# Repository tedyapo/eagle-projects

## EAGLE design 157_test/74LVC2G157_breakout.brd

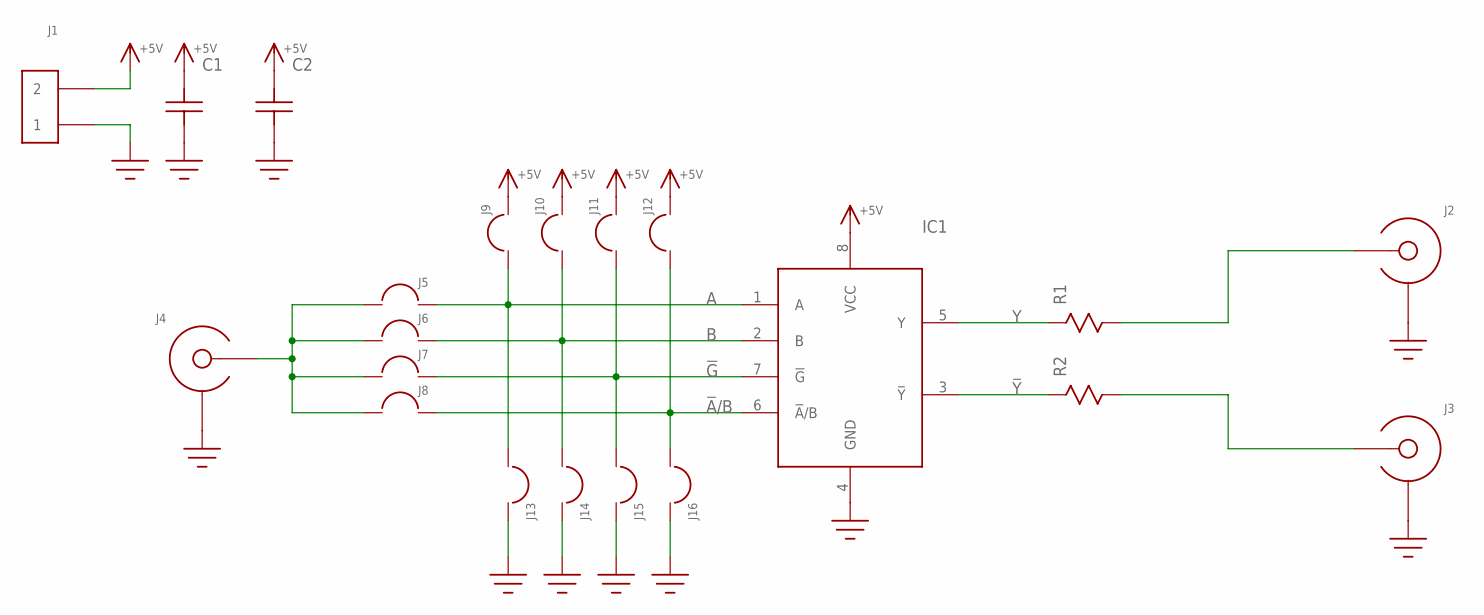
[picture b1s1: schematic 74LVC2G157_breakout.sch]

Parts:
C1: C0603
C2: C1206; 1206
IC1: 74LVC2G157; SSOP8
J1: HEADER_2PIN
J2, J3, J4: EDGE_LAUNCH_JACKNARROW; EDGE_LAUNCH_RF_CON_NARROW
J5, J6, J7, J8, J9, J10, J11, J12, J13, J14, J15, J16: SOLDER_BRIDGE
R1, R2: R0603

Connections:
!A!/B: IC1.6 (!A!/B), J8.2@1, J8.2@2, J8.2@3, J12.1, J16.1
!G!: IC1.7 (!G!), J7.2@1, J7.2@2, J7.2@3, J11.1, J15.1
!Y!: IC1.3 (!Y!), R2.P$1
+5V: C1.P$2, C2.P$2, IC1.8 (VCC), J1.2, J9.2@1, J9.2@2, J9.2@3, J10.2@1, J10.2@2, J10.2@3, J11.2@1, J11.2@2, J11.2@3, J12.2@1, J12.2@2, J12.2@3
A: IC1.1 (A), J5.2@1, J5.2@2, J5.2@3, J9.1, J13.1
B: IC1.2 (B), J6.2@1, J6.2@2, J6.2@3, J10.1, J14.1
GND: C1.P$1, C2.P$1, IC1.4 (GND), J1.1, J2.GND@1 (SHIELD), J2.GND@2 (SHIELD), J2.GND@3 (SHIELD), J2.GND@4 (SHIELD), J2.GND@5 (SHIELD), J2.GND@6 (SHIELD), J2.SHIELD@1 (SHIELD), J2.SHIELD@2 (SHIELD), J3.GND@1 (SHIELD), J3.GND@2 (SHIELD), J3.GND@3 (SHIELD), J3.GND@4 (SHIELD), J3.GND@5 (SHIELD), J3.GND@6 (SHIELD), J3.SHIELD@1 (SHIELD), J3.SHIELD@2 (SHIELD), J4.GND@1 (SHIELD), J4.GND@2 (SHIELD), J4.GND@3 (SHIELD), J4.GND@4 (SHIELD), J4.GND@5 (SHIELD), J4.GND@6 (SHIELD), J4.SHIELD@1 (SHIELD), J4.SHIELD@2 (SHIELD), J13.2@1, J13.2@2, J13.2@3, J14.2@1, J14.2@2, J14.2@3, J15.2@1, J15.2@2, J15.2@3, J16.2@1, J16.2@2, J16.2@3
unnamed: J3.CENTER, R2.P$2
unnamed: J2.CENTER, R1.P$2
unnamed: J4.CENTER, J5.1, J6.1, J7.1, J8.1
Y: IC1.5 (Y), R1.P$1

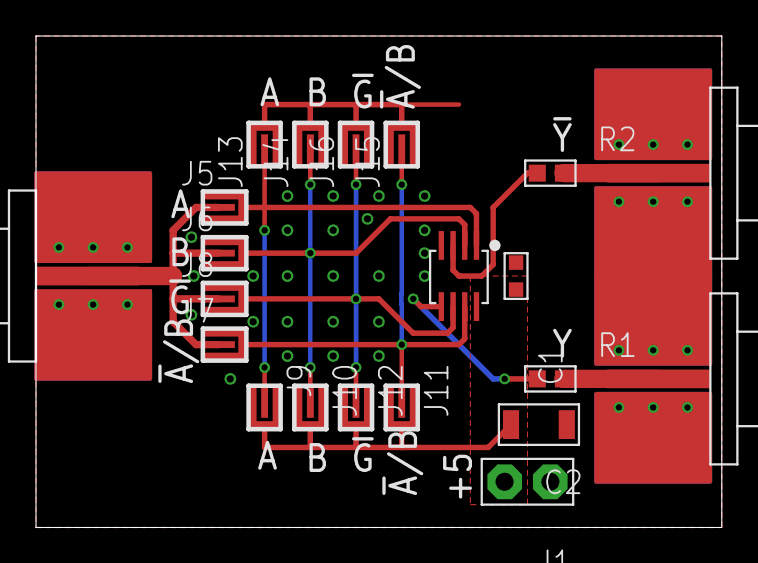
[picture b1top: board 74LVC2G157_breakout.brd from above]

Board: 2 copper layers, 38.1 x 27.3 mm, 21 parts (0 on the bottom side), 11 nets.

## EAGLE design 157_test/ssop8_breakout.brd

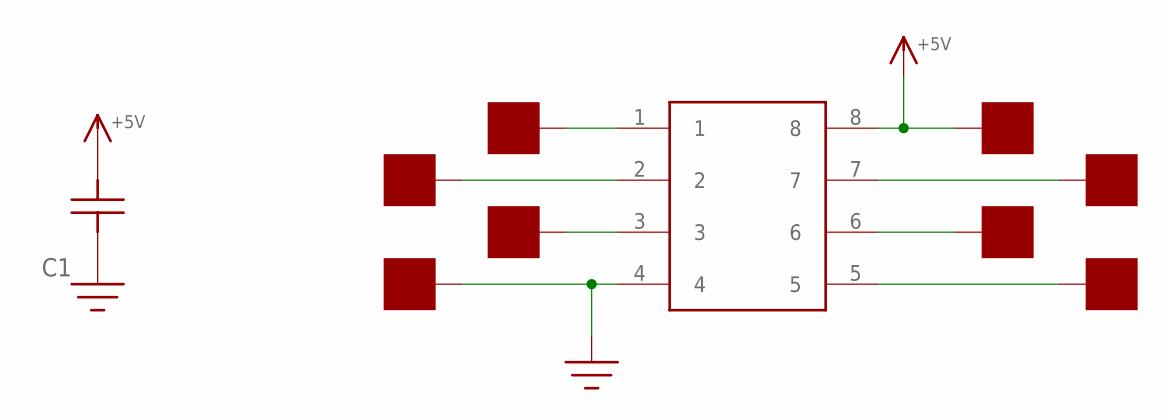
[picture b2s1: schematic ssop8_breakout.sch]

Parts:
C1: C0603
IC1: IC-8PINSSOP8; SSOP8
U$1, U$2, U$3, U$4, U$5, U$6, U$7, U$8: PAD50MIL; PAD_50MIL

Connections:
+5V: C1.P$1, IC1.8, U$1.P$1
GND: C1.P$2, IC1.4, U$8.P$1
unnamed: IC1.1, U$5.P$1
unnamed: IC1.2, U$6.P$1
unnamed: IC1.3, U$7.P$1
unnamed: IC1.7, U$2.P$1
unnamed: IC1.6, U$3.P$1
unnamed: IC1.5, U$4.P$1

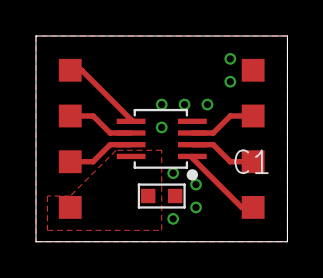
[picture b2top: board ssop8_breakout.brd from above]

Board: 2 copper layers, 14.0 x 11.4 mm, 10 parts (0 on the bottom side), 8 nets.

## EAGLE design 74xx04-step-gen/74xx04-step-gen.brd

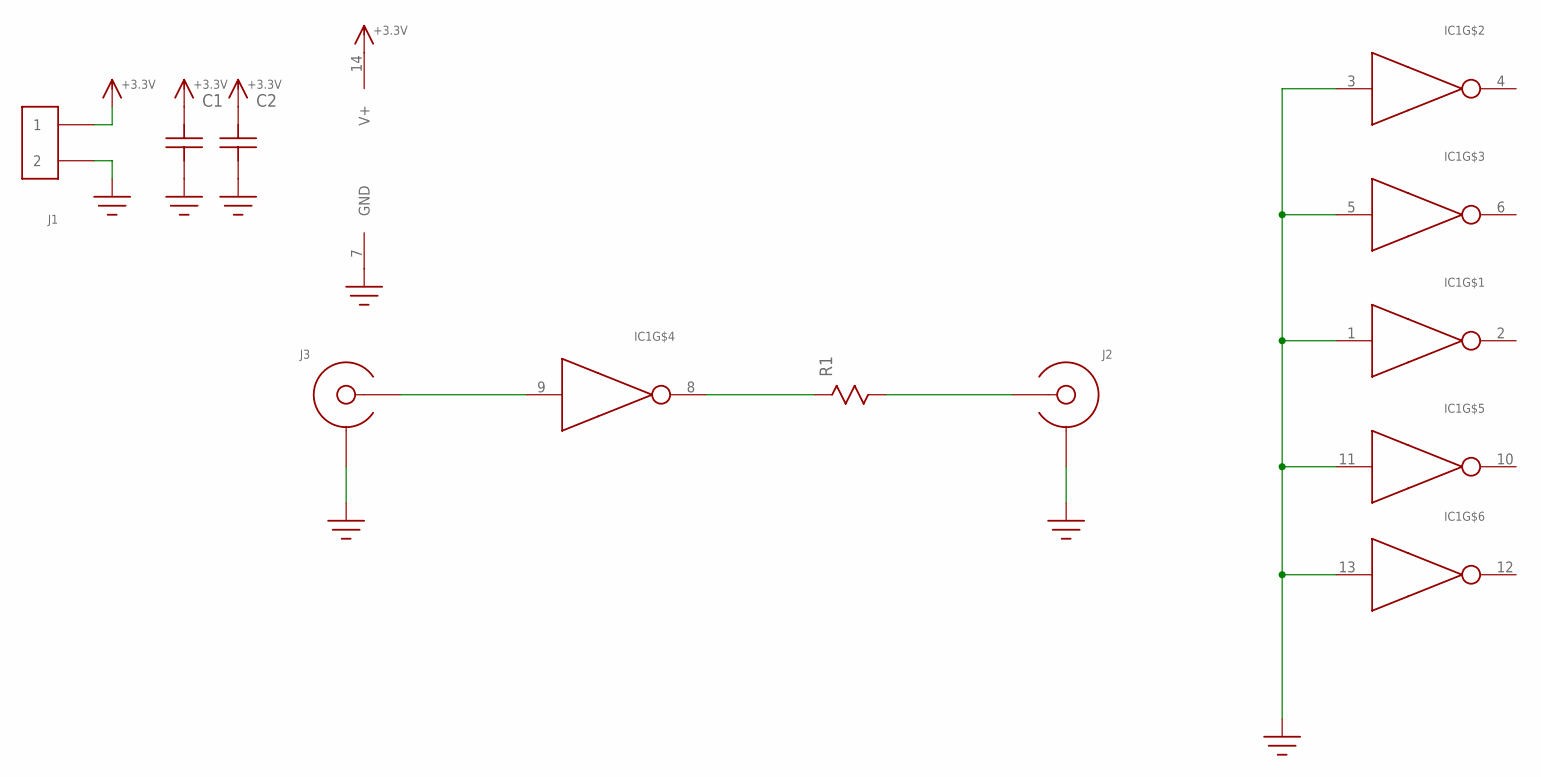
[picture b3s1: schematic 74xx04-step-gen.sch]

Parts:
C1: C1206; 1206
C2: C0603
IC1: 74XX04; SOIC-14
J1: HEADER_2PIN
J2, J3: SMA-EDGE-LAUNCH4020_TAPER; SMA_EDGE_LAUNCH_2L_4020_TAPER
R1: R0603

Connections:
+3.3V: C1.P$2, C2.P$2, IC1.14 (V+), J1.1
GND: C1.P$1, C2.P$1, IC1.1 (IN), IC1.3 (IN), IC1.5 (IN), IC1.7 (GND), IC1.11 (IN), IC1.13 (IN), J1.2, J2.BOTTOM_GND (SHIELD), J2.GND@1 (SHIELD), J2.GND@2 (SHIELD), J2.GND@3 (SHIELD), J2.GND@4 (SHIELD), J2.GND@5 (SHIELD), J2.GND@6 (SHIELD), J2.GND@7 (SHIELD), J2.GND@8 (SHIELD), J2.GND@14 (SHIELD), J2.GND@15 (SHIELD), J2.GND@16 (SHIELD), J2.GND@17 (SHIELD), J2.GND_PAD1 (SHIELD), J2.GND_PAD2 (SHIELD), J2.P$1 (SHIELD), J2.P$2 (SHIELD), J3.BOTTOM_GND (SHIELD), J3.GND@1 (SHIELD), J3.GND@2 (SHIELD), J3.GND@3 (SHIELD), J3.GND@4 (SHIELD), J3.GND@5 (SHIELD), J3.GND@6 (SHIELD), J3.GND@7 (SHIELD), J3.GND@8 (SHIELD), J3.GND@14 (SHIELD), J3.GND@15 (SHIELD), J3.GND@16 (SHIELD), J3.GND@17 (SHIELD), J3.GND_PAD1 (SHIELD), J3.GND_PAD2 (SHIELD), J3.P$1 (SHIELD), J3.P$2 (SHIELD)
unnamed: IC1.9 (IN), J3.CENTER@1 (CENTER)
unnamed: IC1.8 (OUT), R1.P$1
unnamed: J2.CENTER@1 (CENTER), R1.P$2

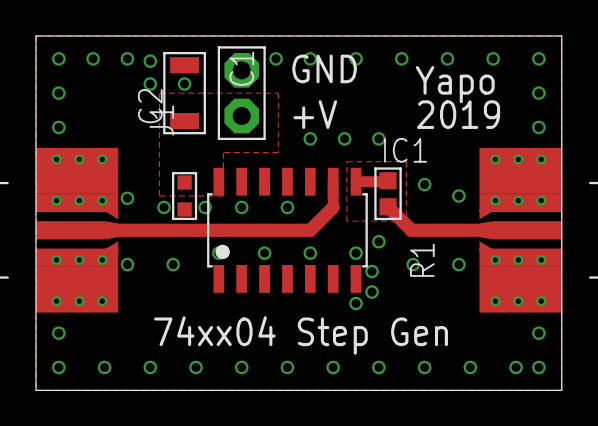
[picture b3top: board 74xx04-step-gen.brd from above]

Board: 2 copper layers, 29.2 x 19.7 mm, 7 parts (0 on the bottom side), 5 nets.

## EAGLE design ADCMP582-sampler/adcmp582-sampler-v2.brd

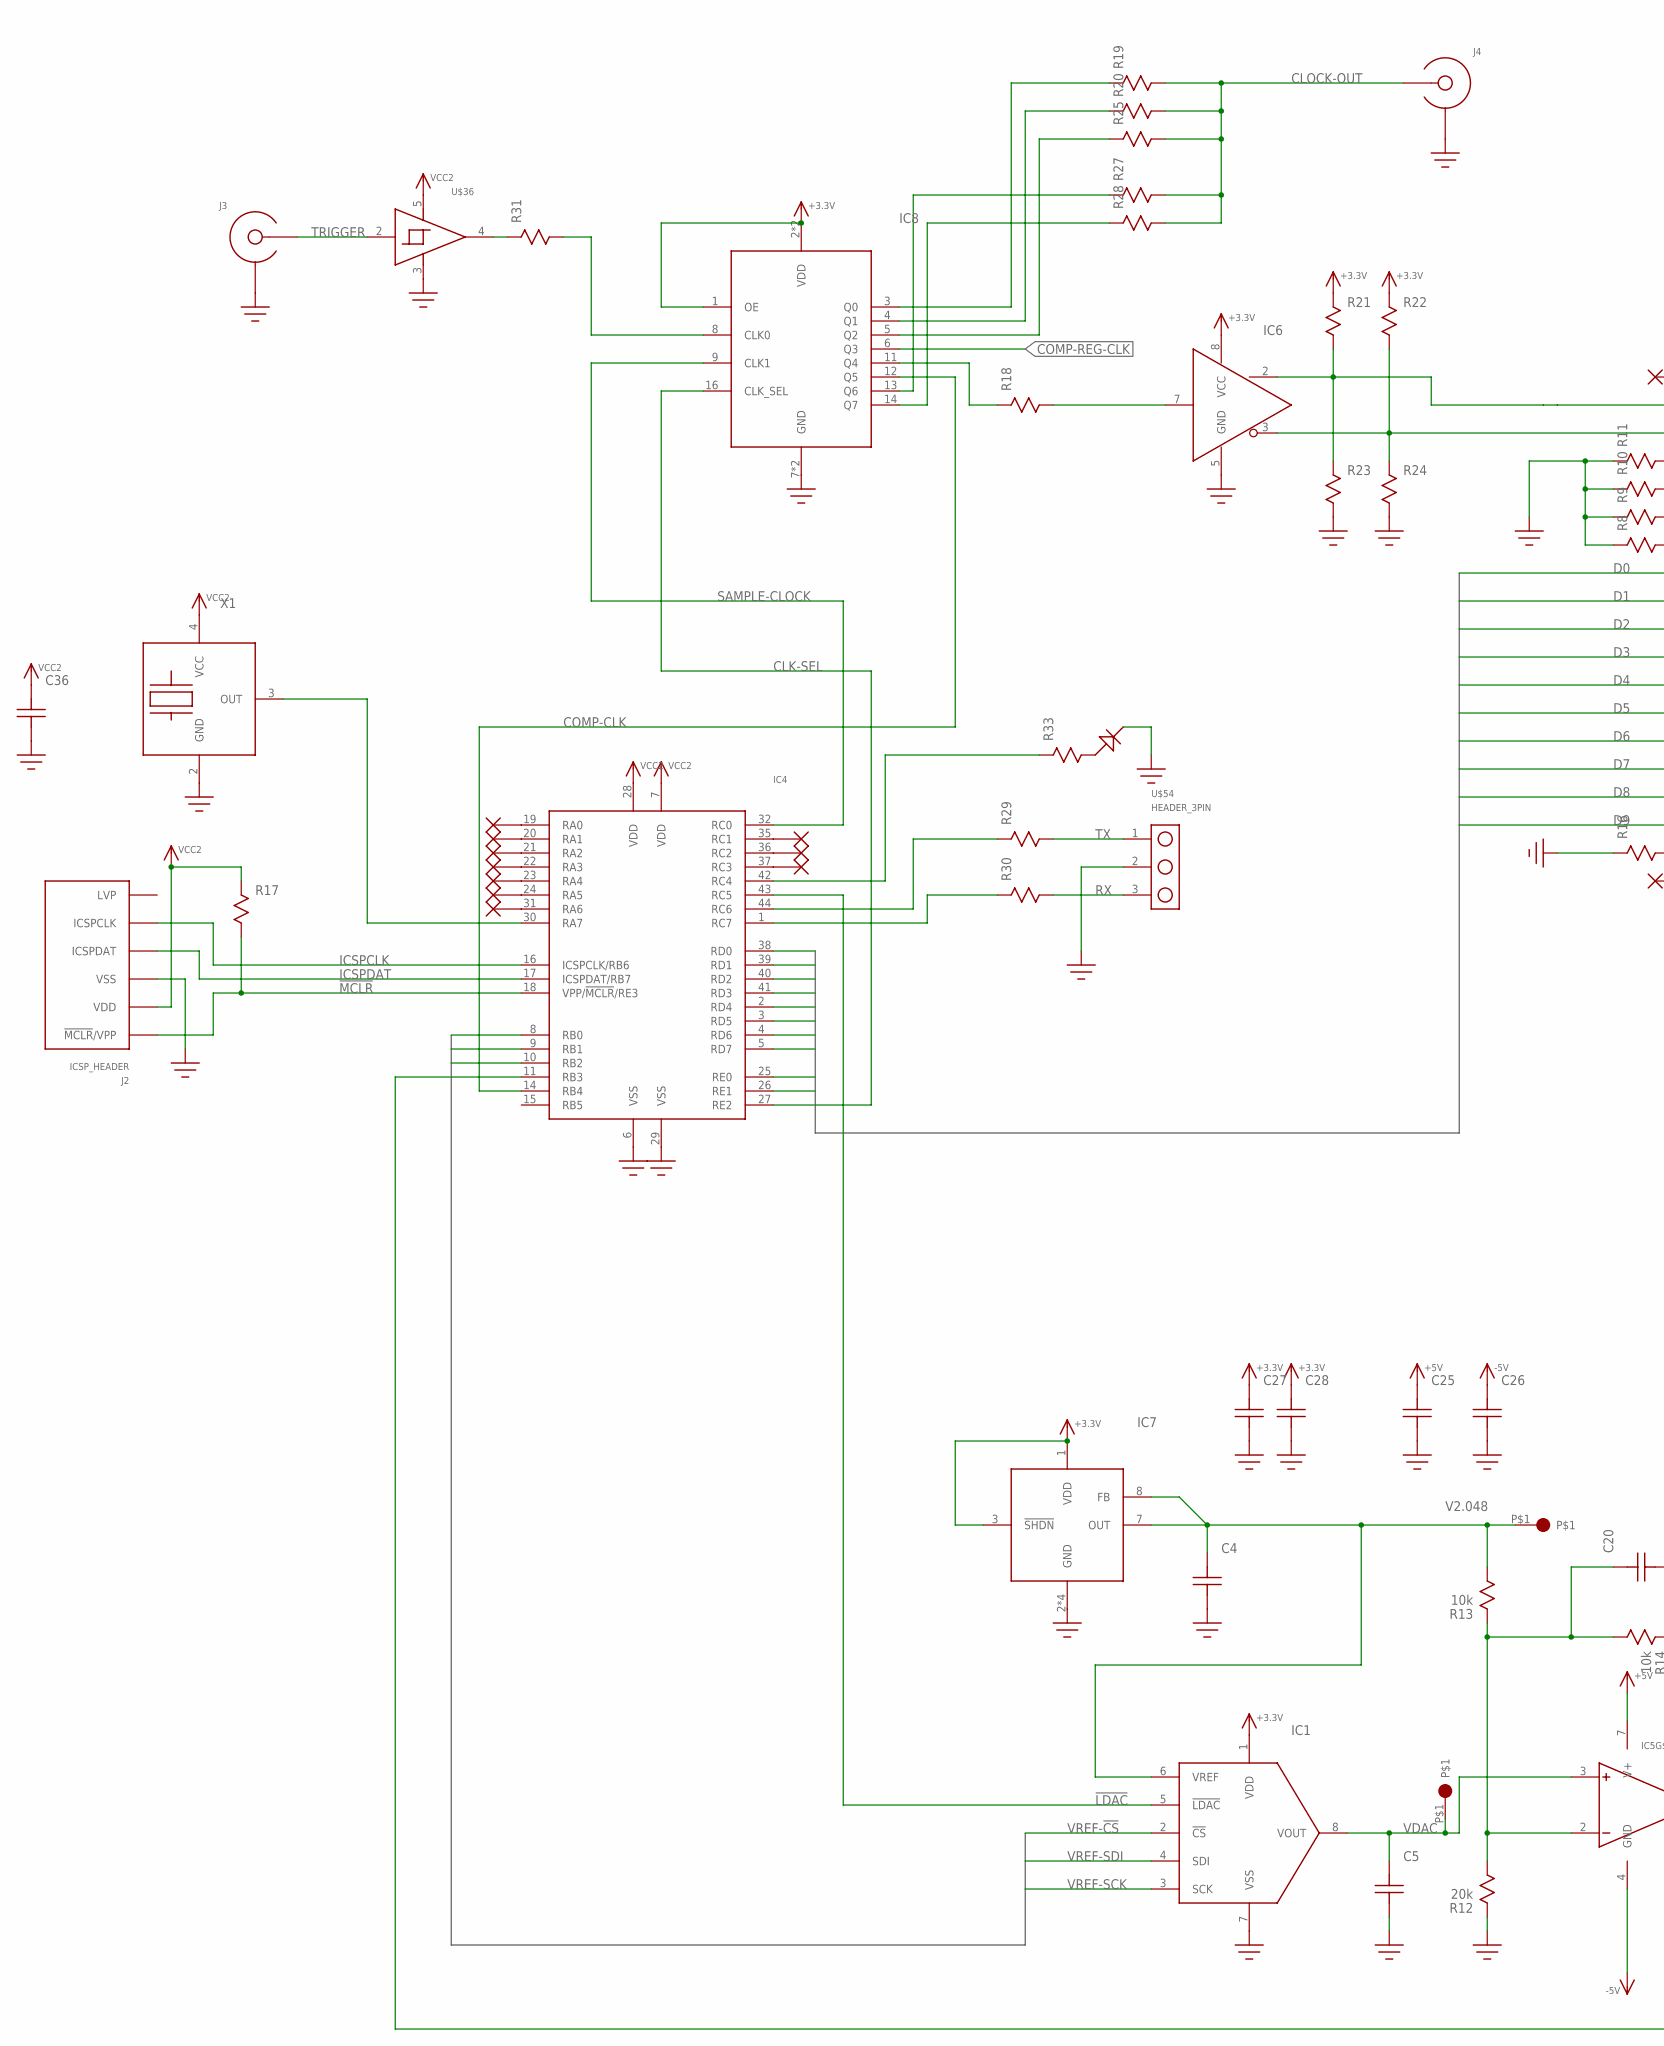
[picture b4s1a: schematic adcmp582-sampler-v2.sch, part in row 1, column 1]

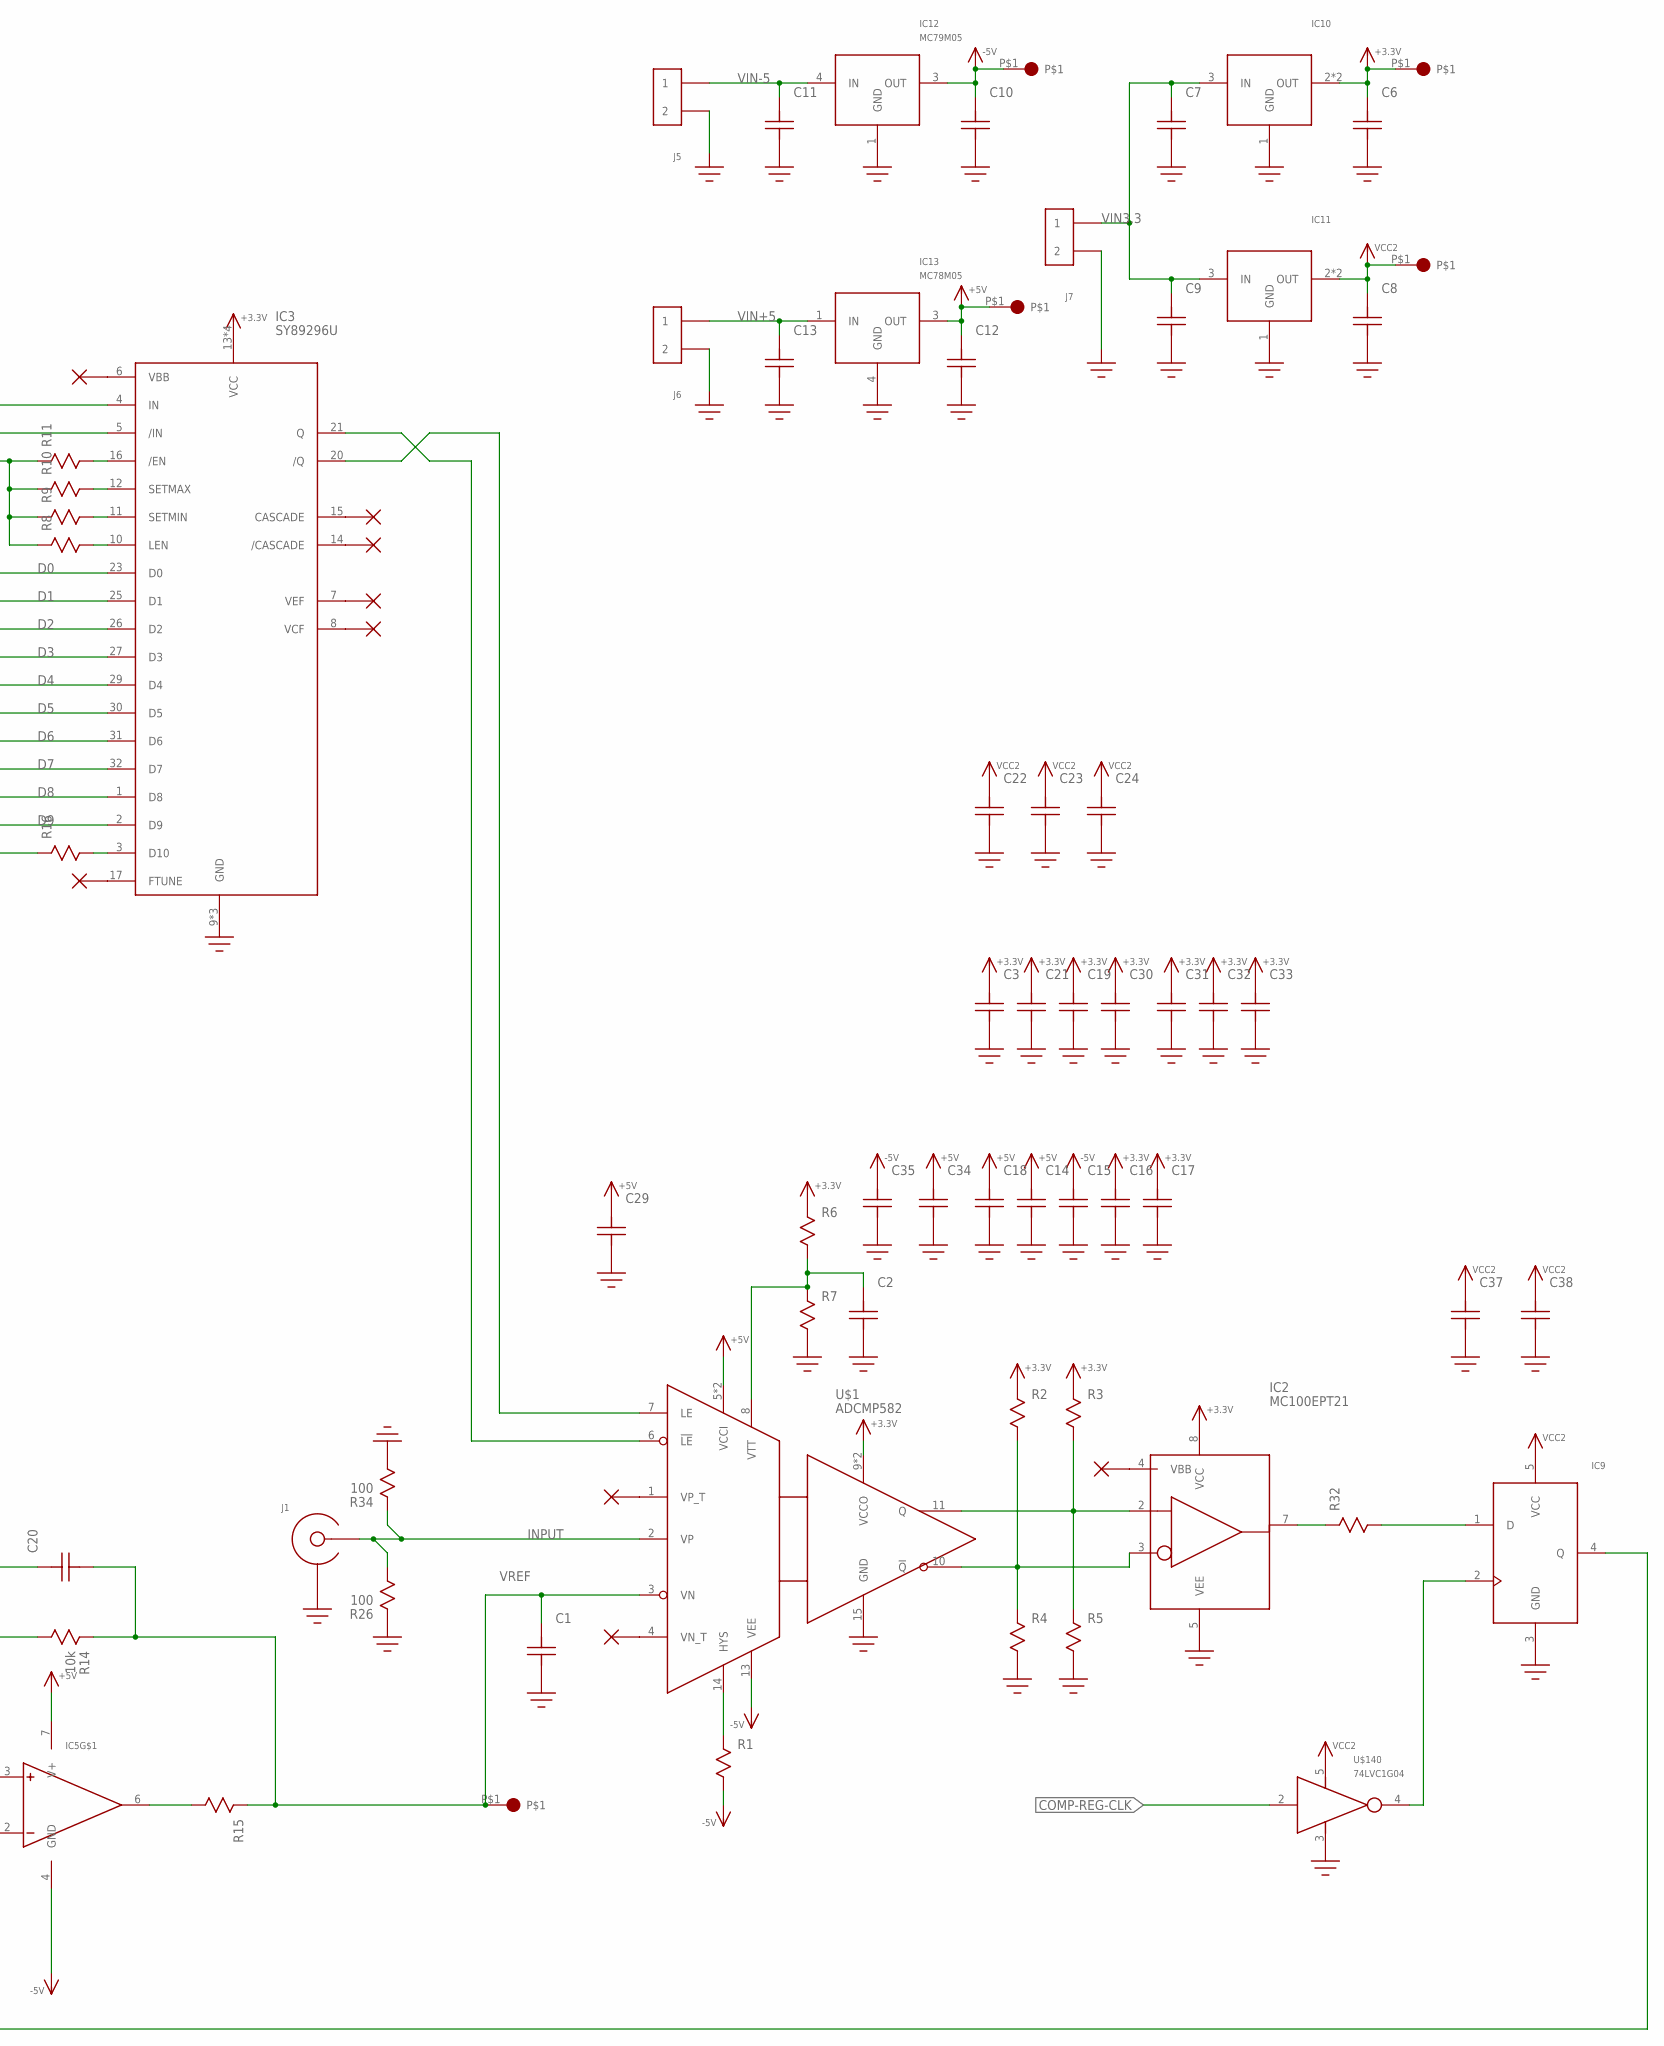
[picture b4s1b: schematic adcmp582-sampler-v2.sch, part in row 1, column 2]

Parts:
C1, C3, C4, C5, C19, C20, C21, C22, C23, C24, C25, C26, C27, C28, C30, C31, C32, C33, C34, C35, C36, C37, C38: C0603
C2, C14, C15, C16, C17, C18: C0402_NO_THERMALS
C6, C7, C8, C9, C10, C11, C12, C13, C29: C1206; 1206
IC1: MCP49X1; SOIC8
IC2: MC100EPT21; SOIC8
IC3: SY89296U; TQFP32_7X7
IC4: PIC16F15376; TQFP44
IC5: ADA4000; SOIC8
IC6: MC100LVELT20; SOIC8
IC7: MCP1501SOIC8; SOIC8
IC8: SI53360TSSOP16; TSSOP16
IC9: 74LVC1G79; SOT23-5
IC10, IC11: AZ1117E; SOT-223
IC12: MC79M05; DPAK
IC13: MC78M05; DPAK
J1, J3, J4: SMA-EDGE-LAUNCH4L-4020-TAPER-FIXED; SMA_EDGE_LAUNCH_4L_4020_TAPER_FIXED
J2: ICSP_HEADER; HEADER_6PIN
J5, J6, J7: HEADER_2PINSCREW-TERM; FCI_20020316_SCREW_TERM_2P
P1, P2, P3, P4, P5, P6, P7: ICSP_PAD
R1, R2, R3, R4, R5, R6, R7, R15, R16, R17, R18, R21, R22, R23, R24, R29, R30, R31, R32, R33: R0603
R8, R9, R10, R11, R19, R20, R25, R27, R28: R0402; 0402
R12: 20k; R0603
R13, R14: 10k; R0603
R26, R34: 100; 0402
U$1: ADCMP582; TQFN16-EP
U$36: 74LVC1G17; SOT23-5
U$54: HEADER_3PIN
U$88: LED_0603
U$140: 74LVC1G04; SOT23-5
X1: XTAL_OSC; XTAL_3.2X5

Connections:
!LDAC!: IC1.5 (!LDAC!), IC4.43 (RC5)
!MCLR!: IC4.18 (VPP/!MCLR!/RE3), J2.1 (!MCLR!/VPP), R17.P$2
+3.3V: C3.P$2, C6.P$2, C16.2, C17.2, C19.P$2, C21.P$2, C27.P$2, C28.P$2, C30.P$2, C31.P$2, C32.P$2, C33.P$2, IC1.1 (VDD), IC2.8 (VCC), IC3.13 (VCC), IC3.18 (VCC), IC3.19 (VCC), IC3.22 (VCC), IC6.8 (VCC), IC7.1 (VDD), IC7.3 (!SHDN!), IC8.1 (OE), IC8.2 (VDD), IC8.15 (VDD), IC10.2 (OUT), IC10.4 (OUT), P5.P$1, R2.P$1, R3.P$1, R6.P$1, R21.P$1, R22.P$1, U$1.9 (VCCO), U$1.12 (VCCO)
+5V: C12.P$2, C14.2, C18.2, C25.P$2, C29.P$2, C34.P$2, IC5.7 (V+), IC13.3 (OUT), P4.P$1, U$1.5 (VCCI), U$1.16 (VCCI)
-5V: C10.P$2, C15.2, C26.P$2, C35.P$2, IC5.4 (GND), IC12.3 (OUT), P3.P$1, R1.P$2, U$1.13 (VEE)
CLK-SEL: IC4.27 (RE2), IC8.16 (CLK_SEL)
CLOCK-OUT: J4.CENTER@1 (CENTER), J4.P$3 (CENTER), R19.2, R20.2, R25.2, R27.2, R28.2
COMP-CLK: IC4.14 (RB4), IC8.12 (Q5)
COMP-OUT: IC4.11 (RB3), IC9.4 (Q)
COMP-REG-CLK: IC8.6 (Q3), U$140.2 (IN)
D0: IC3.23 (D0), IC4.38 (RD0)
D1: IC3.25 (D1), IC4.39 (RD1)
D2: IC3.26 (D2), IC4.40 (RD2)
D3: IC3.27 (D3), IC4.41 (RD3)
D4: IC3.29 (D4), IC4.2 (RD4)
D5: IC3.30 (D5), IC4.3 (RD5)
D6: IC3.31 (D6), IC4.4 (RD6)
D7: IC3.32 (D7), IC4.5 (RD7)
D8: IC3.1 (D8), IC4.25 (RE0)
D9: IC3.2 (D9), IC4.26 (RE1)
GND: C1.P$1, C2.1, C3.P$1, C4.P$1, C5.P$1, C6.P$1, C7.P$1, C8.P$1, C9.P$1, C10.P$1, C11.P$1, C12.P$1, C13.P$1, C14.1, C15.1, C16.1, C17.1, C18.1, C19.P$1, C21.P$1, C22.P$1, C23.P$1, C24.P$1, C25.P$1, C26.P$1, C27.P$1, C28.P$1, C29.P$1, C30.P$1, C31.P$1, C32.P$1, C33.P$1, C34.P$1, C35.P$1, C36.P$1, C37.P$1, C38.P$1, IC1.7 (VSS), IC2.5 (VEE), IC3.9 (GND), IC3.24 (GND), IC3.28 (GND), IC4.6 (VSS), IC4.29 (VSS), IC6.5 (GND), IC7.2 (GND), IC7.4 (GND), IC7.5 (GND), IC7.6 (GND), IC8.7 (GND), IC8.10 (GND), IC9.3 (GND), IC10.1 (GND), IC11.1 (GND), IC12.1 (GND), IC13.4 (GND), J1.BOTTOM_GND (SHIELD), J1.GND@1 (SHIELD), J1.GND@2 (SHIELD), J1.GND@3 (SHIELD), J1.GND@4 (SHIELD), J1.GND@5 (SHIELD), J1.GND@6 (SHIELD), J1.GND@7 (SHIELD), J1.GND@8 (SHIELD), J1.GND@14 (SHIELD), J1.GND@15 (SHIELD), J1.GND@16 (SHIELD), J1.GND@17 (SHIELD), J1.GND_PAD1 (SHIELD), J1.GND_PAD2 (SHIELD), J1.P$1 (SHIELD), J1.P$2 (SHIELD), J2.3 (VSS), J3.BOTTOM_GND (SHIELD), J3.GND@1 (SHIELD), J3.GND@2 (SHIELD), J3.GND@3 (SHIELD), J3.GND@4 (SHIELD), J3.GND@5 (SHIELD), J3.GND@6 (SHIELD), J3.GND@7 (SHIELD), J3.GND@8 (SHIELD), J3.GND@14 (SHIELD), J3.GND@15 (SHIELD), J3.GND@16 (SHIELD), J3.GND@17 (SHIELD), J3.GND_PAD1 (SHIELD), J3.GND_PAD2 (SHIELD), J3.P$1 (SHIELD), J3.P$2 (SHIELD), J4.BOTTOM_GND (SHIELD), J4.GND@1 (SHIELD), J4.GND@2 (SHIELD), J4.GND@3 (SHIELD), J4.GND@4 (SHIELD), J4.GND@5 (SHIELD), J4.GND@6 (SHIELD), J4.GND@7 (SHIELD), J4.GND@8 (SHIELD), J4.GND@14 (SHIELD), J4.GND@15 (SHIELD), J4.GND@16 (SHIELD), J4.GND@17 (SHIELD), J4.GND_PAD1 (SHIELD), J4.GND_PAD2 (SHIELD), J4.P$1 (SHIELD), J4.P$2 (SHIELD), J5.P$2 (2), J6.P$2 (2), J7.P$2 (2), R4.P$2, R5.P$2, R7.P$2, R8.1, R9.1, R10.1, R11.1, R12.P$1, R16.P$1, R23.P$2, R24.P$2, R26.1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
ICSPCLK: IC4.16 (ICSPCLK/RB6), J2.5 (ICSPCLK)
ICSPDAT: IC4.17 (ICSPDAT/RB7), J2.4 (ICSPDAT)
INPUT: J1.CENTER@1 (CENTER), J1.P$3 (CENTER), R26.2, R34.1, U$1.2 (VP)
LE_N: IC3.21 (Q), U$1.6 (!LE!)
LE_P1: IC3.20 (/Q), U$1.7 (LE)
unnamed: R31.P$1, U$36.4 (OUT)
unnamed: R1.P$1, U$1.14 (HYS)
unnamed: IC2.2 (D), R3.P$2, R5.P$1, U$1.11 (Q)
unnamed: IC2.3 (!D!), R2.P$2, R4.P$1, U$1.10 (!Q!)
unnamed: C2.2, R6.P$2, R7.P$1, U$1.8 (VTT)
unnamed: IC3.16 (/EN), R11.2
unnamed: IC3.12 (SETMAX), R10.2
unnamed: IC3.11 (SETMIN), R9.2
unnamed: IC3.10 (LEN), R8.2
unnamed: IC3.4 (IN), IC6.2 (Q), R21.P$2, R23.P$1
unnamed: IC2.7 (Q), R32.P$1
unnamed: IC8.11 (Q4), R18.P$1
unnamed: IC9.2 (CLK), U$140.4 (OUT)
unnamed: C20.P$2, IC5.2 (-), R12.P$2, R13.P$1, R14.P$2
unnamed: IC3.5 (/IN), IC6.3 (!Q!), R22.P$2, R24.P$1
unnamed: IC8.8 (CLK0), R31.P$2
unnamed: IC4.30 (RA7), X1.3 (OUT)
unnamed: IC4.42 (RC4), R33.P$1
unnamed: R33.P$2, U$88.A
unnamed: IC9.1 (D), R32.P$2
unnamed: IC5.6 (OUT), R15.P$2
unnamed: IC3.3 (D10), R16.P$2
unnamed: IC6.7 (D), R18.P$2
unnamed: IC8.14 (Q7), R28.1
unnamed: IC8.13 (Q6), R27.1
unnamed: IC8.5 (Q2), R25.1
unnamed: IC8.4 (Q1), R20.1
unnamed: IC8.3 (Q0), R19.1
unnamed: IC4.44 (RC6), R29.P$1
unnamed: IC4.1 (RC7), R30.P$1
RX: R30.P$2, U$54.3
SAMPLE-CLOCK: IC4.32 (RC0), IC8.9 (CLK1)
TRIGGER: J3.CENTER@1 (CENTER), J3.P$3 (CENTER), U$36.2 (IN)
TX: R29.P$2, U$54.1
V2.048: C4.P$2, IC1.6 (VREF), IC7.7 (OUT), IC7.8 (FB), P7.P$1, R13.P$2
VCC2: C8.P$2, C22.P$2, C23.P$2, C24.P$2, C36.P$2, C37.P$2, C38.P$2, IC4.7 (VDD), IC4.28 (VDD), IC9.5 (VCC), IC11.2 (OUT), IC11.4 (OUT), J2.2 (VDD), P6.P$1, R17.P$1, U$36.5 (VCC), U$140.5 (VCC), X1.4 (VCC)
VDAC: C5.P$2, IC1.8 (VOUT), IC5.3 (+), P2.P$1
VIN3.3: C7.P$2, C9.P$2, IC10.3 (IN), IC11.3 (IN), J7.P$1 (1)
VIN+5: C13.P$2, IC13.1 (IN), J6.P$1 (1)
VIN-5: C11.P$2, IC12.4 (IN), J5.P$1 (1)
VREF: C1.P$2, C20.P$1, P1.P$1, R14.P$1, R15.P$1, U$1.3 (VN)
VREF-!CS!: IC1.2 (!CS!), IC4.8 (RB0)
VREF-SCK: IC1.3 (SCK), IC4.9 (RB1)
VREF-SDI: IC1.4 (SDI), IC4.10 (RB2)

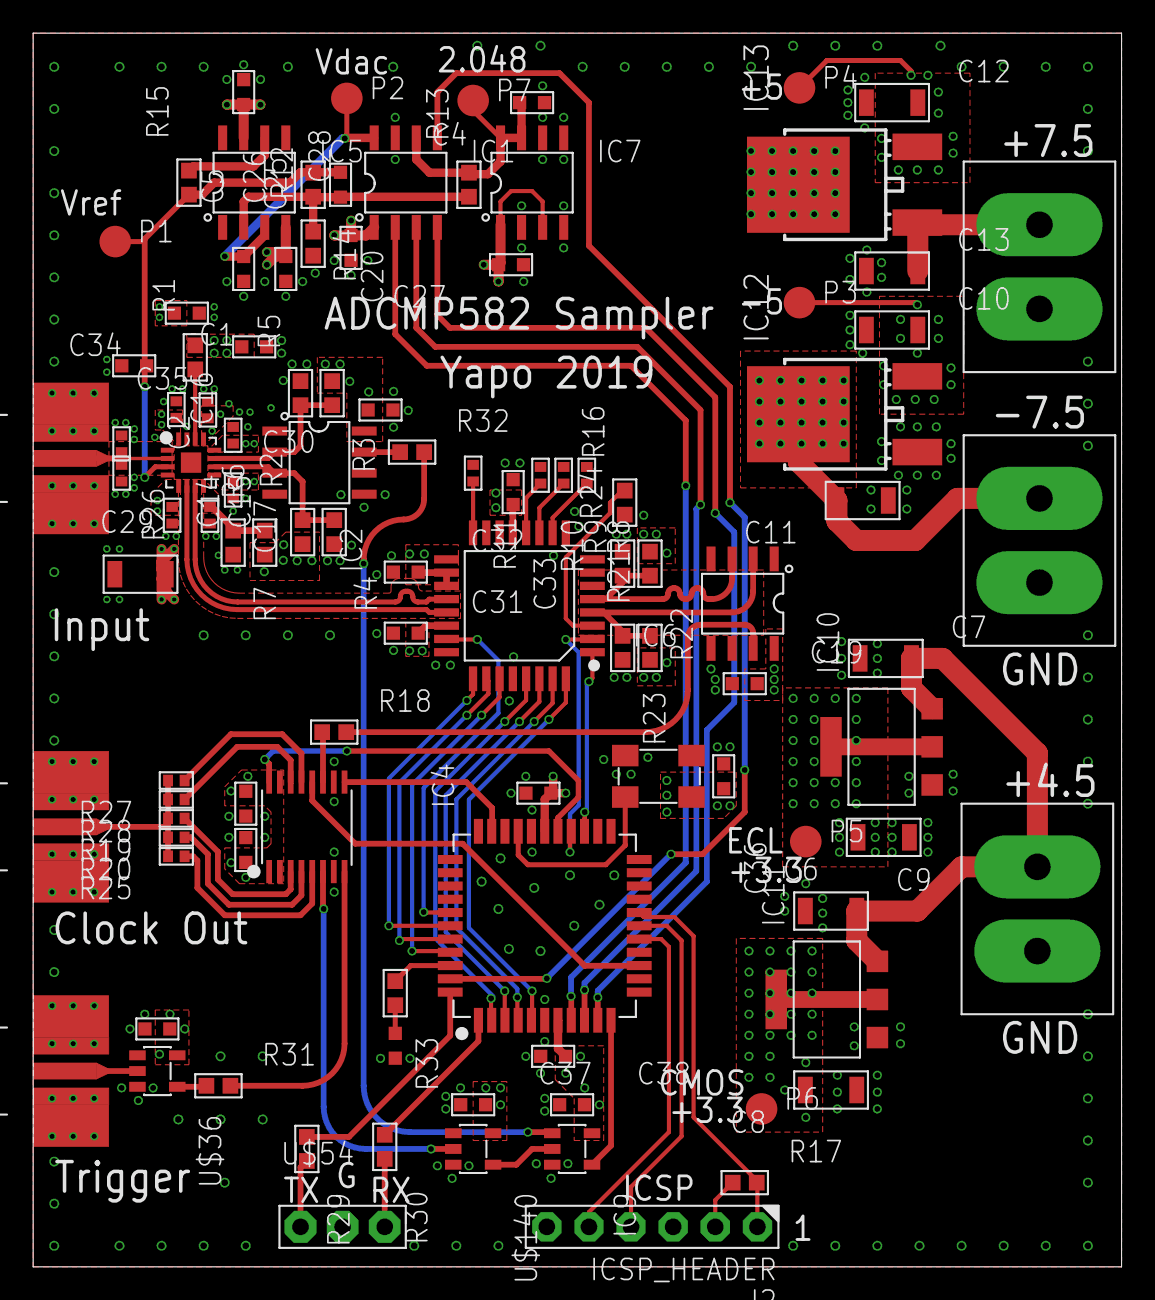
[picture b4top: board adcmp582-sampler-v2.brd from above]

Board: 4 copper layers, 65.7 x 74.4 mm, 105 parts (0 on the bottom side), 70 nets.

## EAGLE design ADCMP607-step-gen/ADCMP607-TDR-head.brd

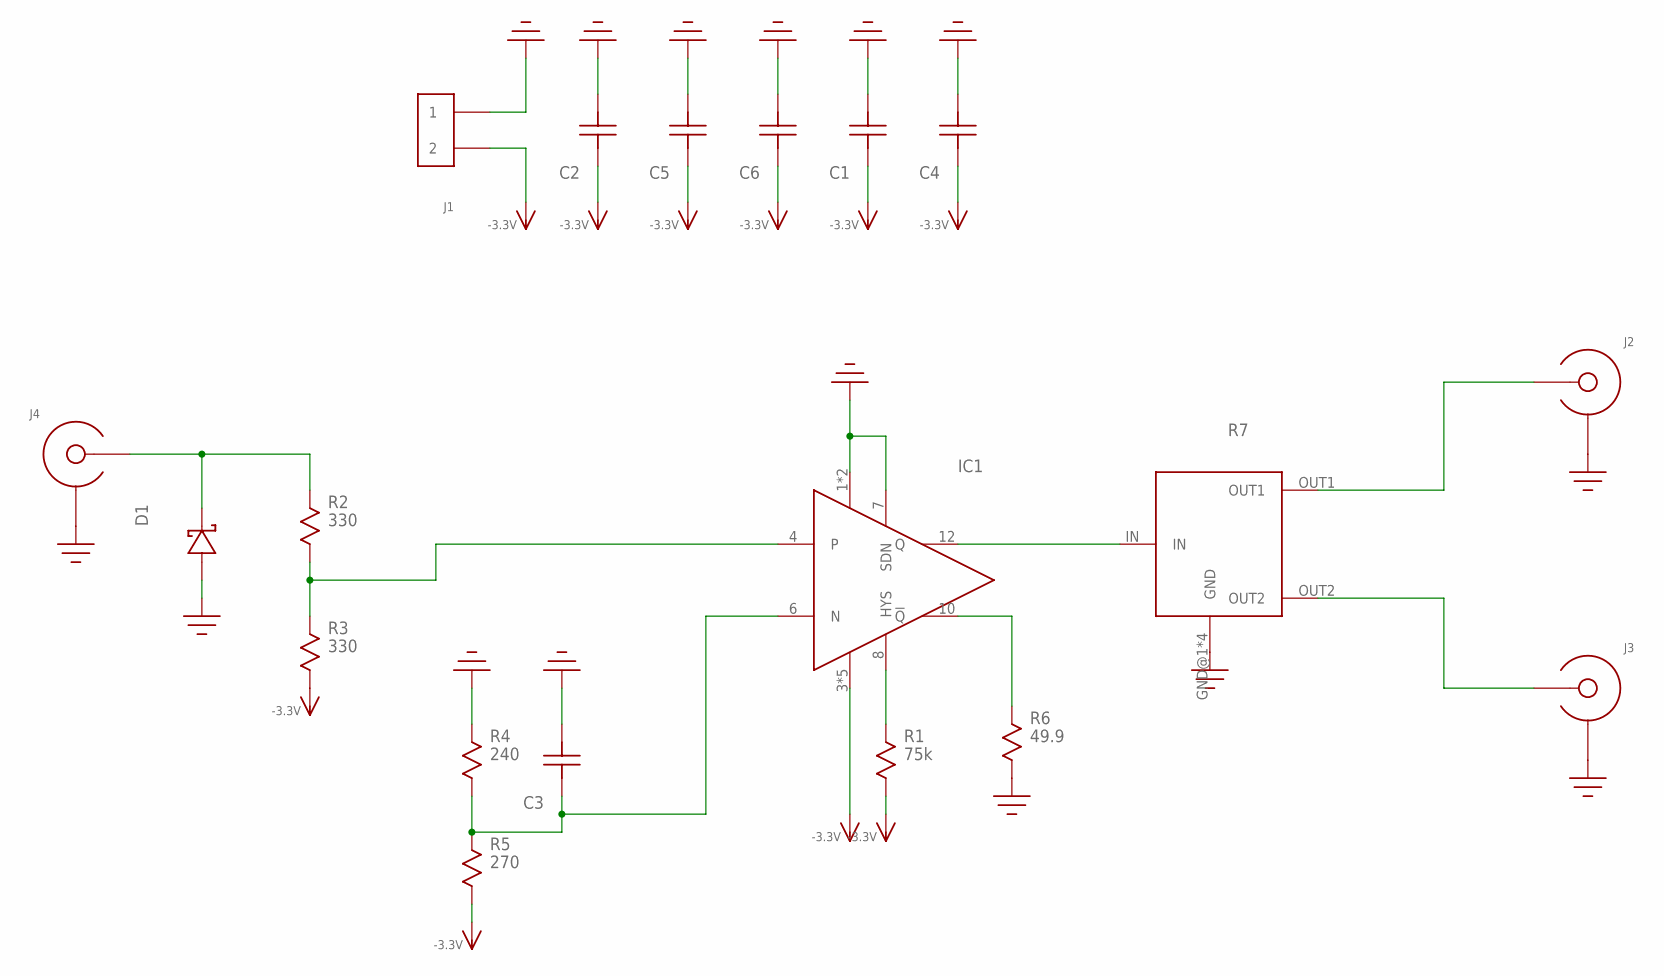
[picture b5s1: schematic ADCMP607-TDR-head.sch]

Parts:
C1, C3, C4, C5, C6: C0603
C2: C1206; 1206
D1: SCHOTTKYSOT-23; SOT-23
IC1: ADCMP607; QFN12-3X3
J1: HEADER_2PIN
J2, J3, J4: SMA-EDGE-LAUNCH4020_TAPER; SMA_EDGE_LAUNCH_2L_4020_TAPER
R1: 75k; R0603
R2, R3: 330; R0603
R4: 240; R0603
R5: 270; R0603
R6: 49.9; 0402
R7: PS2012G-SPLITTER

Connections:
-3.3V: C1.P$2, C2.P$2, C4.P$2, C5.P$2, C6.P$2, IC1.3 (VEE), IC1.5 (VEE), IC1.9 (VEE), IC1.11 (VEE), IC1.EP (VEE), J1.2, R1.P$2, R3.P$2, R5.P$2
GND: C1.P$1, C2.P$1, C3.P$1, C4.P$1, C5.P$1, C6.P$1, D1.1 (ANODE), IC1.1 (VCC), IC1.2 (VCC), IC1.7 (SDN), J1.1, J2.BOTTOM_GND (SHIELD), J2.GND@1 (SHIELD), J2.GND@2 (SHIELD), J2.GND@3 (SHIELD), J2.GND@4 (SHIELD), J2.GND@5 (SHIELD), J2.GND@6 (SHIELD), J2.GND@7 (SHIELD), J2.GND@8 (SHIELD), J2.GND@14 (SHIELD), J2.GND@15 (SHIELD), J2.GND@16 (SHIELD), J2.GND@17 (SHIELD), J2.GND_PAD1 (SHIELD), J2.GND_PAD2 (SHIELD), J2.P$1 (SHIELD), J2.P$2 (SHIELD), J3.BOTTOM_GND (SHIELD), J3.GND@1 (SHIELD), J3.GND@2 (SHIELD), J3.GND@3 (SHIELD), J3.GND@4 (SHIELD), J3.GND@5 (SHIELD), J3.GND@6 (SHIELD), J3.GND@7 (SHIELD), J3.GND@8 (SHIELD), J3.GND@14 (SHIELD), J3.GND@15 (SHIELD), J3.GND@16 (SHIELD), J3.GND@17 (SHIELD), J3.GND_PAD1 (SHIELD), J3.GND_PAD2 (SHIELD), J3.P$1 (SHIELD), J3.P$2 (SHIELD), J4.BOTTOM_GND (SHIELD), J4.GND@1 (SHIELD), J4.GND@2 (SHIELD), J4.GND@3 (SHIELD), J4.GND@4 (SHIELD), J4.GND@5 (SHIELD), J4.GND@6 (SHIELD), J4.GND@7 (SHIELD), J4.GND@8 (SHIELD), J4.GND@14 (SHIELD), J4.GND@15 (SHIELD), J4.GND@16 (SHIELD), J4.GND@17 (SHIELD), J4.GND_PAD1 (SHIELD), J4.GND_PAD2 (SHIELD), J4.P$1 (SHIELD), J4.P$2 (SHIELD), R4.P$1, R6.2, R7.GND@1 (GND), R7.GND@2 (GND), R7.GND@3 (GND), R7.GND@4 (GND)
unnamed: C3.P$2, IC1.6 (N), R4.P$2, R5.P$1
unnamed: IC1.8 (HYS), R1.P$1
unnamed: IC1.12 (Q), R7.IN
unnamed: IC1.10 (!Q!), R6.1
unnamed: D1.3 (CATHODE), J4.CENTER@1 (CENTER), R2.P$1
unnamed: IC1.4, R2.P$2, R3.P$1
unnamed: J2.CENTER@1 (CENTER), R7.OUT1
unnamed: J3.CENTER@1 (CENTER), R7.OUT2

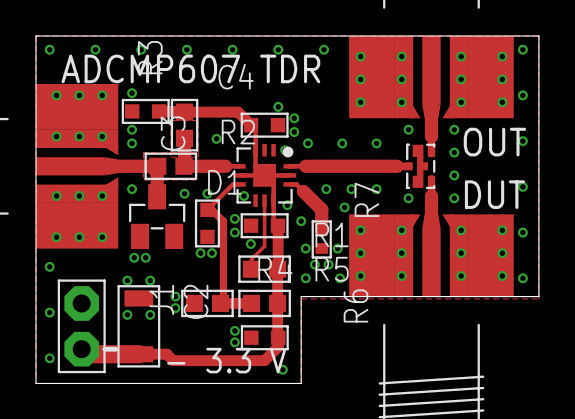
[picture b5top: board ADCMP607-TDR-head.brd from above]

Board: 2 copper layers, 27.9 x 19.3 mm, 19 parts (0 on the bottom side), 10 nets.

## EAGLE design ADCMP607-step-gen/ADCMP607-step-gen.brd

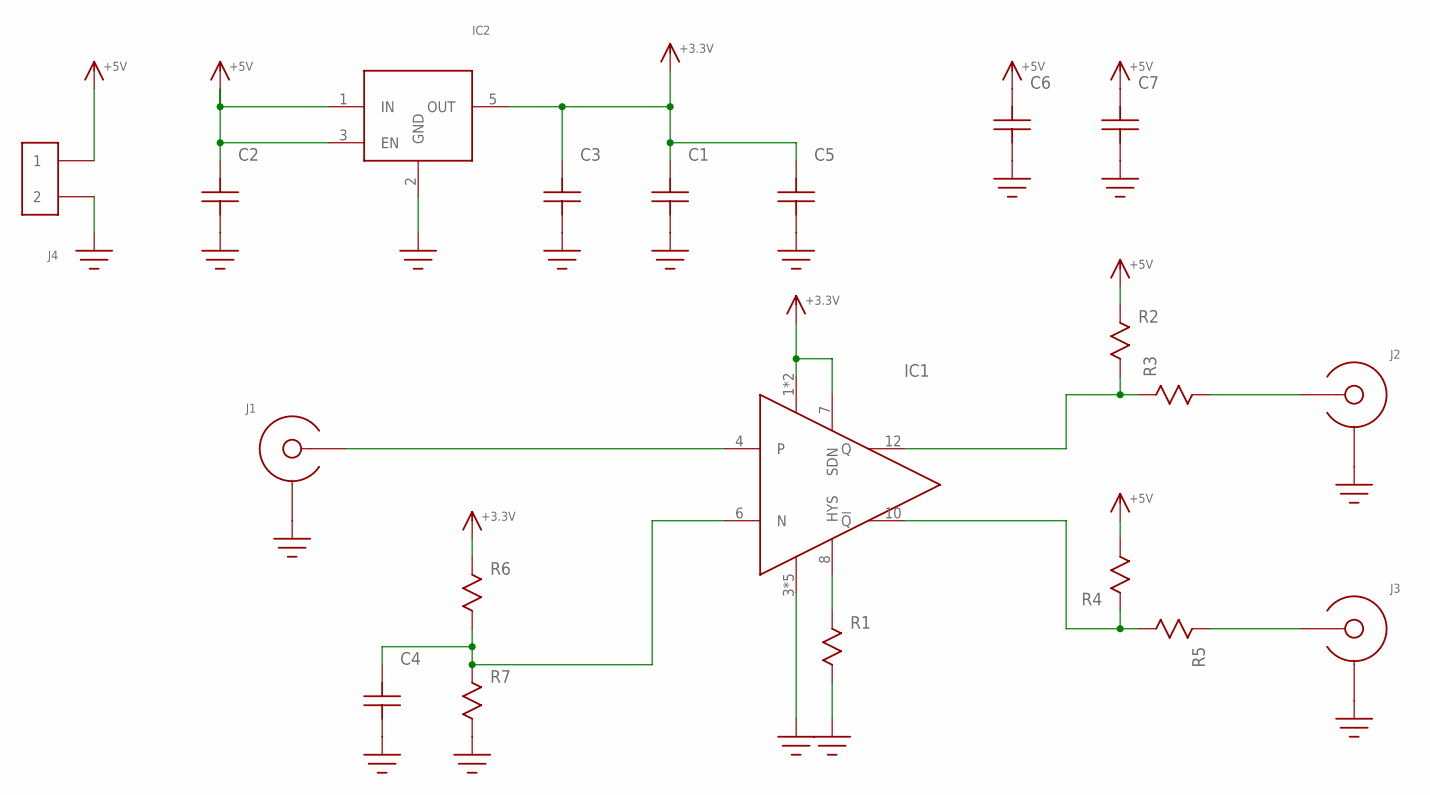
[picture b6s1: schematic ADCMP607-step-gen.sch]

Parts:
C1, C5, C6, C7: C; C0402
C2: C1206; 1206
C3, C4: C0603
IC1: ADCMP607; QFN12-3X3
IC2: MIC5501; SOT23-5
J1, J2, J3: SMA-EDGE-LAUNCH4L-4020-TAPER-FIXED; SMA_EDGE_LAUNCH_4L_4020_TAPER_FIXED
J4: HEADER_2PIN
R1, R6, R7: R0603
R2, R3, R4, R5: R0402; 0402

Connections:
+3.3V: C1.2, C3.P$2, C5.2, IC1.1 (VCC), IC1.2 (VCC), IC1.7 (SDN), IC2.5 (OUT), R6.P$1
+5V: C2.P$2, C6.2, C7.2, IC2.1 (IN), IC2.3 (EN), J4.1, R2.1, R4.2
GND: C1.1, C2.P$1, C3.P$1, C4.P$1, C5.1, C6.1, C7.1, IC1.3 (VEE), IC1.5 (VEE), IC1.9 (VEE), IC1.11 (VEE), IC1.EP (VEE), IC2.2 (GND), J1.BOTTOM_GND (SHIELD), J1.GND@1 (SHIELD), J1.GND@2 (SHIELD), J1.GND@3 (SHIELD), J1.GND@4 (SHIELD), J1.GND@5 (SHIELD), J1.GND@6 (SHIELD), J1.GND@7 (SHIELD), J1.GND@8 (SHIELD), J1.GND@14 (SHIELD), J1.GND@15 (SHIELD), J1.GND@16 (SHIELD), J1.GND@17 (SHIELD), J1.GND_PAD1 (SHIELD), J1.GND_PAD2 (SHIELD), J1.P$1 (SHIELD), J1.P$2 (SHIELD), J2.BOTTOM_GND (SHIELD), J2.GND@1 (SHIELD), J2.GND@2 (SHIELD), J2.GND@3 (SHIELD), J2.GND@4 (SHIELD), J2.GND@5 (SHIELD), J2.GND@6 (SHIELD), J2.GND@7 (SHIELD), J2.GND@8 (SHIELD), J2.GND@14 (SHIELD), J2.GND@15 (SHIELD), J2.GND@16 (SHIELD), J2.GND@17 (SHIELD), J2.GND_PAD1 (SHIELD), J2.GND_PAD2 (SHIELD), J2.P$1 (SHIELD), J2.P$2 (SHIELD), J3.BOTTOM_GND (SHIELD), J3.GND@1 (SHIELD), J3.GND@2 (SHIELD), J3.GND@3 (SHIELD), J3.GND@4 (SHIELD), J3.GND@5 (SHIELD), J3.GND@6 (SHIELD), J3.GND@7 (SHIELD), J3.GND@8 (SHIELD), J3.GND@14 (SHIELD), J3.GND@15 (SHIELD), J3.GND@16 (SHIELD), J3.GND@17 (SHIELD), J3.GND_PAD1 (SHIELD), J3.GND_PAD2 (SHIELD), J3.P$1 (SHIELD), J3.P$2 (SHIELD), J4.2, R1.P$2, R7.P$2
unnamed: IC1.8 (HYS), R1.P$1
unnamed: J2.CENTER@1 (CENTER), J2.P$3 (CENTER), R3.2
unnamed: J3.CENTER@1 (CENTER), J3.P$3 (CENTER), R5.1
unnamed: IC1.12 (Q), R2.2, R3.1
unnamed: IC1.10 (!Q!), R4.1, R5.2
unnamed: C4.P$2, IC1.6 (N), R6.P$2, R7.P$1
unnamed: IC1.4, J1.CENTER@1 (CENTER), J1.P$3 (CENTER)

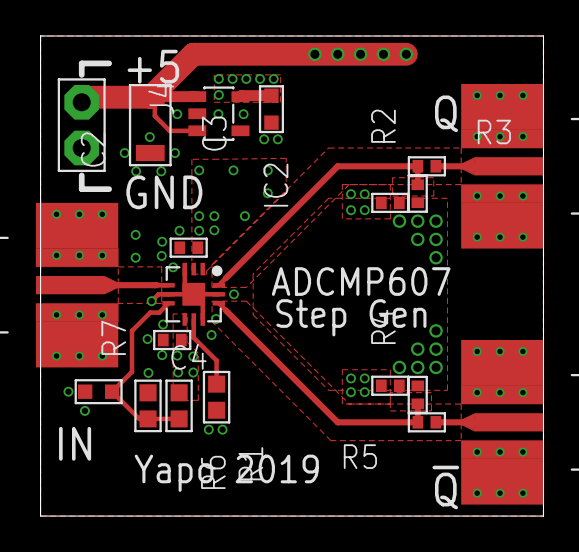
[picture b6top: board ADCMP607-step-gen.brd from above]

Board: 4 copper layers, 27.9 x 26.7 mm, 20 parts (0 on the bottom side), 10 nets.
